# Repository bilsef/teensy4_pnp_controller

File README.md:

# teensy4_pnp_controller

# UNTESTED - USE AT YOUR OWN RISK
Preliminary testing shows everything working

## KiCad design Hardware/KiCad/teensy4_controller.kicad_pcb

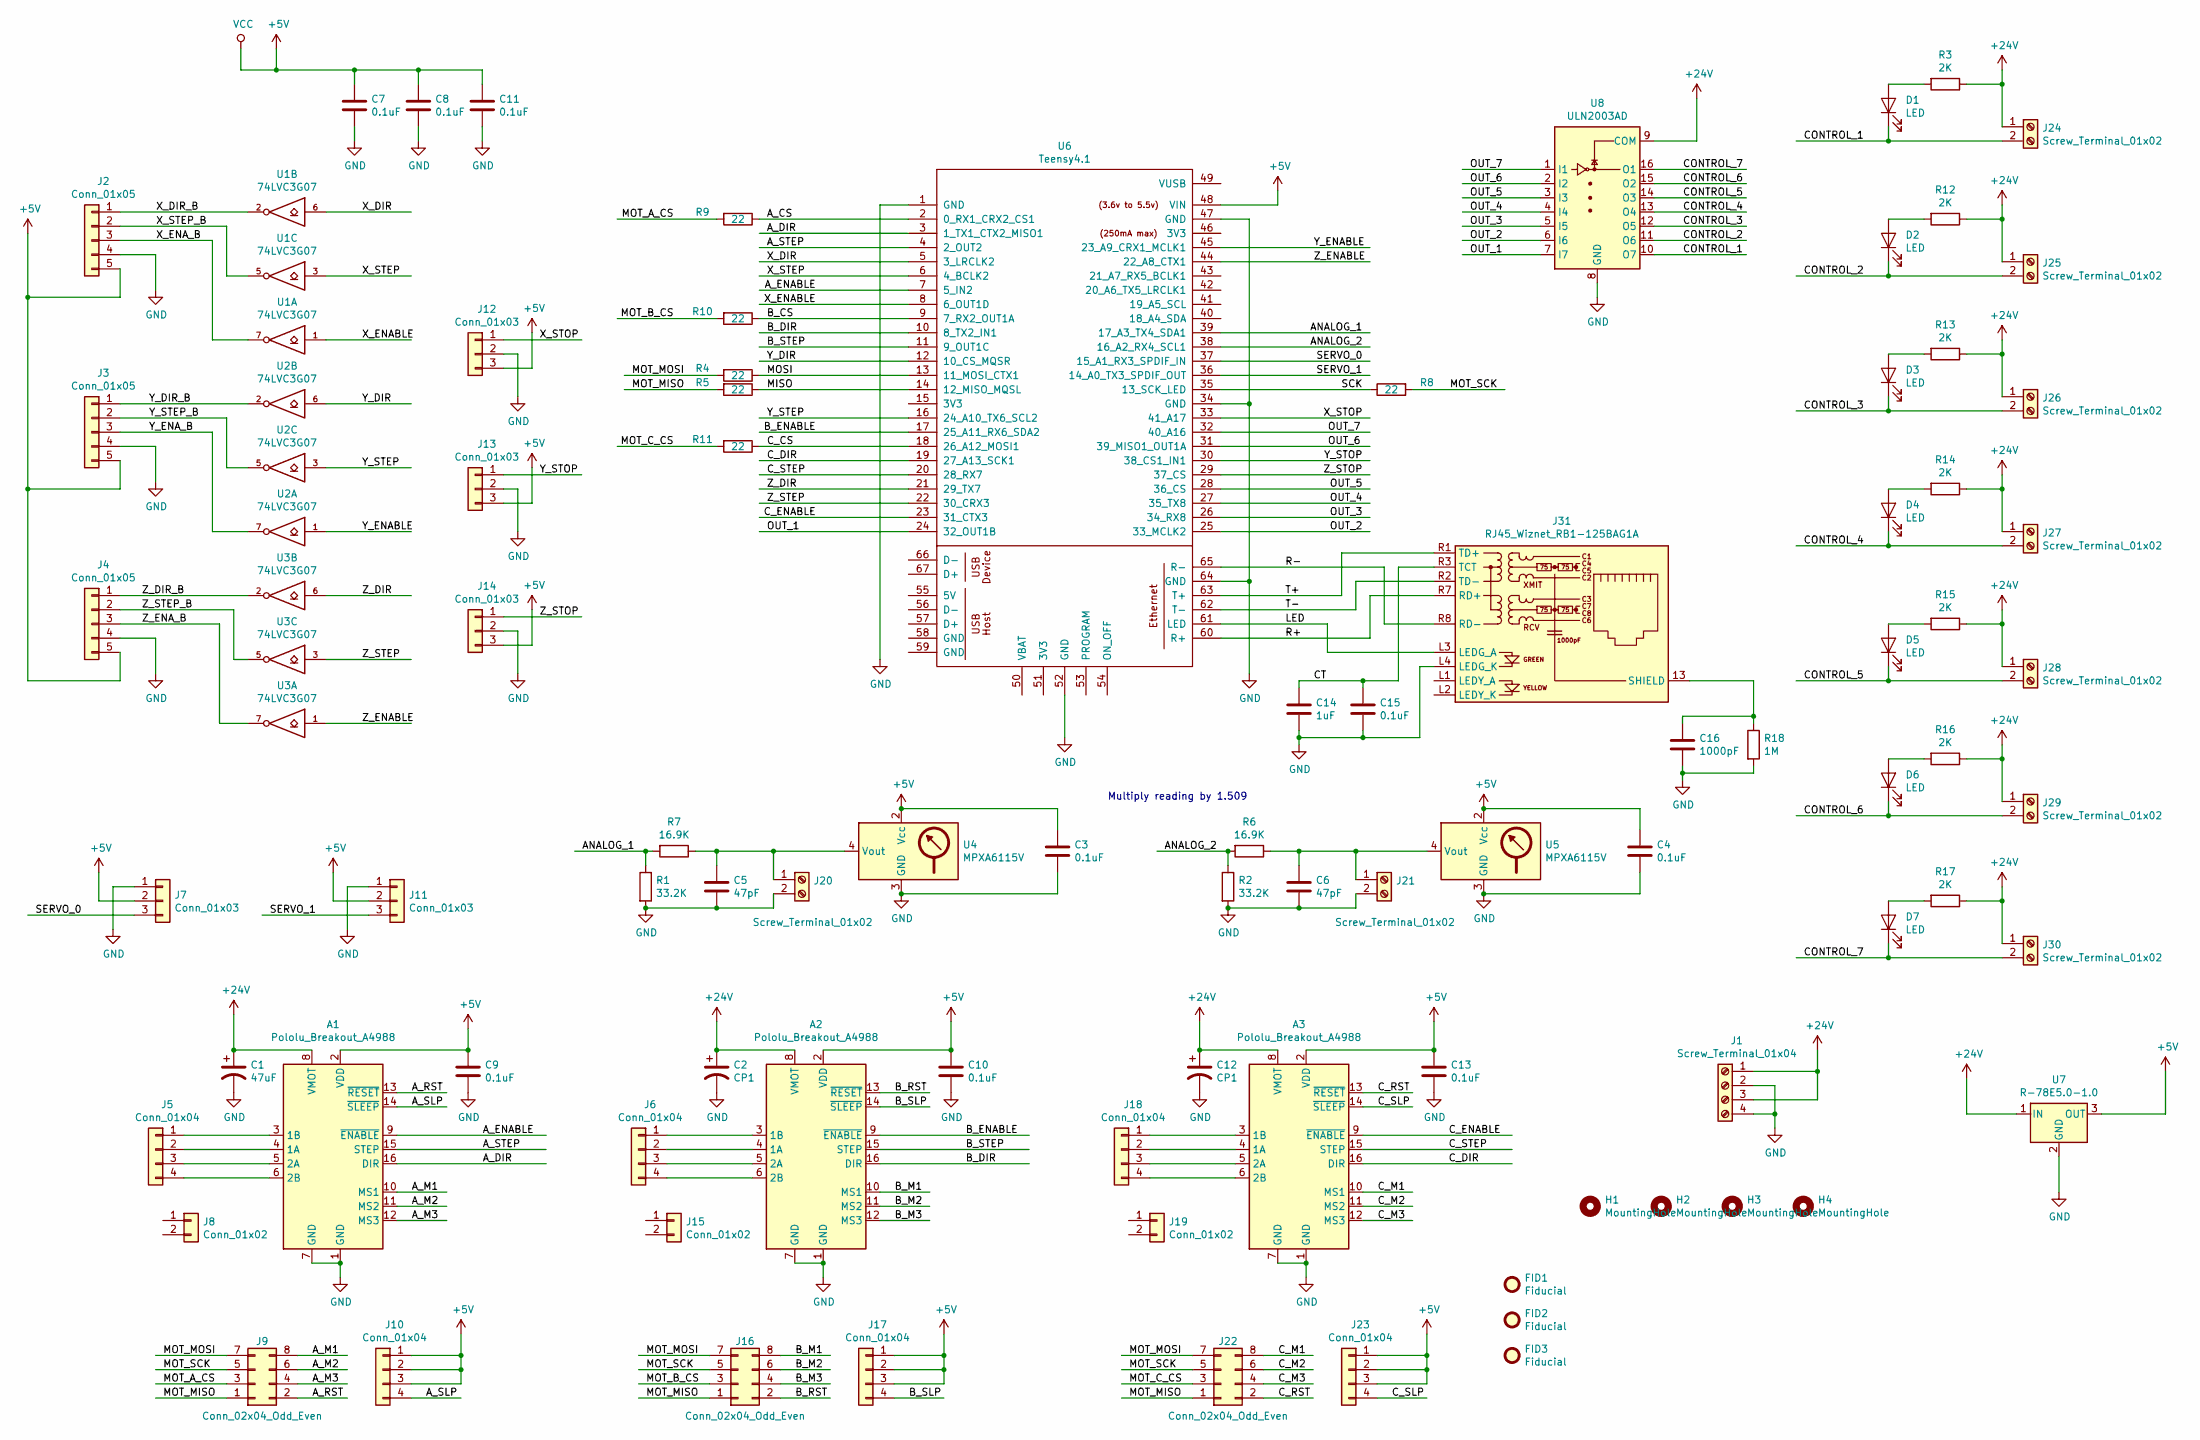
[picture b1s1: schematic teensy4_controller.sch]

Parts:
A1, A2, A3: Pololu_Breakout_A4988; Pololu_Breakout-16_15.2x20.3mm
C1: 47uF; CP_Elec_6.3x7.7
C2, C12: CP1; CP_Elec_6.3x7.7
C3, C4, C7, C8, C9, C10, C11, C13, C15: 0.1uF; C_0603_1608Metric_Pad1.05x0.95mm_HandSolder
C5, C6: 47pF; C_0603_1608Metric_Pad1.05x0.95mm_HandSolder
C14: 1uF; C_0805_2012Metric_Pad1.15x1.40mm_HandSolder
C16: 1000pF; C_1210_3225Metric_Pad1.42x2.65mm_HandSolder
D1, D2, D3, D4, D5, D6, D7: LED; LED_0603_1608Metric_Pad1.05x0.95mm_HandSolder
FID1, FID2, FID3: Fiducial; Fiducial_1mm_Mask3mm
H1, H2, H3, H4: MountingHole; MountingHole_3.2mm_M3
J1: Screw_Terminal_01x04; TerminalBlock_Phoenix_MKDS-1,5-4_1x04_P5.00mm_Horizontal
J2, J3, J4: Conn_01x05; JST_XH_B5B-XH-AM_1x05_P2.50mm_Vertical
J5, J6, J18: Conn_01x04; JST_XH_B4B-XH-A_1x04_P2.50mm_Vertical
J7, J11: Conn_01x03; PinHeader_1x03_P2.54mm_Vertical
J8, J15, J19: Conn_01x02; PinHeader_1x02_P2.54mm_Vertical
J9, J16, J22: Conn_02x04_Odd_Even; PinHeader_2x04_P2.54mm_Vertical
J10, J17, J23: Conn_01x04; PinHeader_1x04_P2.54mm_Vertical
J12, J13, J14: Conn_01x03; JST_XH_B3B-XH-AM_1x03_P2.50mm_Vertical
J20, J21, J24, J25, J26, J27, J28, J29, J30: Screw_Terminal_01x02; TerminalBlock_Phoenix_PT-1,5-2-3.5-H_1x02_P3.50mm_Horizontal
J31: RJ45_Wiznet_RB1-125BAG1A; RJ45_Amphenol_RJMG1BD3B8K1ANR
R1, R2: 33.2K; R_0603_1608Metric_Pad1.05x0.95mm_HandSolder
R3, R12, R13, R14, R15, R16, R17: 2K; R_0603_1608Metric_Pad1.05x0.95mm_HandSolder
R4, R5, R8, R9, R10, R11: 22; R_0603_1608Metric_Pad1.05x0.95mm_HandSolder
R6, R7: 16.9K; R_0603_1608Metric_Pad1.05x0.95mm_HandSolder
R18: 1M; R_0603_1608Metric_Pad1.05x0.95mm_HandSolder
U1, U2, U3: 74LVC3G07; VSSOP-8_3.0x3.0mm_P0.65mm
U4, U5: MPXA6115V; MPXA6115A
U6: Teensy4.1; Teensy41
U7: R-78E5.0-1.0; Converter_DCDC_RECOM_R-78E-0.5_THT
U8: ULN2003AD; SOIC-16_3.9x9.9mm_P1.27mm

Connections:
+5V: A1.2 (VDD), A2.2 (VDD), A3.2 (VDD), C3.1, C4.1, C7.1, C8.1, C9.1, C10.1, C11.1, C13.1, J2.5, J3.5, J4.5, J7.2, J10.1, J10.2, J10.3, J11.2, J12.3, J13.3, J14.3, J17.1, J17.2, J17.3, J23.1, J23.2, J23.3, U1.8 (VCC), U2.8 (VCC), U3.8 (VCC), U4.2 (Vcc), U5.2 (Vcc), U6.48 (VIN), U7.3 (OUT)
+24V: A1.8 (VMOT), A2.8 (VMOT), A3.8 (VMOT), C1.1, C2.1, C12.1, J1.1, J1.3, J24.1, J25.1, J26.1, J27.1, J28.1, J29.1, J30.1, R3.1, R12.1, R13.1, R14.1, R15.1, R16.1, R17.1, U7.1 (IN), U8.9 (COM)
/ANALOG_1: R1.1, R7.2, U6.39 (17_A3_TX4_SDA1)
/ANALOG_2: R2.1, R6.2, U6.38 (16_A2_RX4_SCL1)
/A_CS: R9.1, U6.2 (0_RX1_CRX2_CS1)
/A_DIR: A1.16 (DIR), U6.3 (1_TX1_CTX2_MISO1)
/A_ENABLE: A1.9 (~ENABLE), U6.7 (5_IN2)
/A_M1: A1.10 (MS1), J9.8
/A_M2: A1.11 (MS2), J9.6
/A_M3: A1.12 (MS3), J9.4
/A_RST: A1.13 (~RESET), J9.2
/A_SLP: A1.14 (~SLEEP), J10.4
/A_STEP: A1.15 (STEP), U6.4 (2_OUT2)
/B_CS: R10.1, U6.9 (7_RX2_OUT1A)
/B_DIR: A2.16 (DIR), U6.10 (8_TX2_IN1)
/B_ENABLE: A2.9 (~ENABLE), U6.17 (25_A11_RX6_SDA2)
/B_M1: A2.10 (MS1), J16.8
/B_M2: A2.11 (MS2), J16.6
/B_M3: A2.12 (MS3), J16.4
/B_RST: A2.13 (~RESET), J16.2
/B_SLP: A2.14 (~SLEEP), J17.4
/B_STEP: A2.15 (STEP), U6.11 (9_OUT1C)
/CONTROL_1: D1.1 (K), J24.2, U8.10 (O7)
/CONTROL_2: D2.1 (K), J25.2, U8.11 (O6)
/CONTROL_3: D3.1 (K), J26.2, U8.12 (O5)
/CONTROL_4: D4.1 (K), J27.2, U8.13 (O4)
/CONTROL_5: D5.1 (K), J28.2, U8.14 (O3)
/CONTROL_6: D6.1 (K), J29.2, U8.15 (O2)
/CONTROL_7: D7.1 (K), J30.2, U8.16 (O1)
/CT: C14.1, C15.1, J31.R3 (TCT)
/C_CS: R11.1, U6.18 (26_A12_MOSI1)
/C_DIR: A3.16 (DIR), U6.19 (27_A13_SCK1)
/C_ENABLE: A3.9 (~ENABLE), U6.23 (31_CTX3)
/C_M1: A3.10 (MS1), J22.8
/C_M2: A3.11 (MS2), J22.6
/C_M3: A3.12 (MS3), J22.4
/C_RST: A3.13 (~RESET), J22.2
/C_SLP: A3.14 (~SLEEP), J23.4
/C_STEP: A3.15 (STEP), U6.20 (28_RX7)
/LED: J31.L3 (LEDG_A), U6.61 (LED)
/MISO: R5.1, U6.14 (12_MISO_MQSL)
/MOSI: R4.1, U6.13 (11_MOSI_CTX1)
/MOT_A_CS: J9.3, R9.2
/MOT_B_CS: J16.3, R10.2
/MOT_C_CS: J22.3, R11.2
/MOT_MISO: J9.1, J16.1, J22.1, R5.2
/MOT_MOSI: J9.7, J16.7, J22.7, R4.2
/MOT_SCK: J9.5, J16.5, J22.5, R8.2
/OUT_1: U6.24 (32_OUT1B), U8.7 (I7)
/OUT_2: U6.25 (33_MCLK2), U8.6 (I6)
/OUT_3: U6.26 (34_RX8), U8.5 (I5)
/OUT_4: U6.27 (35_TX8), U8.4 (I4)
/OUT_5: U6.28 (36_CS), U8.3 (I3)
/OUT_6: U6.31 (39_MISO1_OUT1A), U8.2 (I2)
/OUT_7: U6.32 (40_A16), U8.1 (I1)
/R+: J31.R7 (RD+), U6.60 (R+)
/R-: J31.R8 (RD-), U6.65 (R-)
/SCK: R8.1, U6.35 (13_SCK_LED)
/SERVO_0: J7.3, U6.37 (15_A1_RX3_SPDIF_IN)
/SERVO_1: J11.3, U6.36 (14_A0_TX3_SPDIF_OUT)
/T+: J31.R1 (TD+), U6.63 (T+)
/T-: J31.R2 (TD-), U6.62 (T-)
/X_DIR: U1.6, U6.5 (3_LRCLK2)
/X_DIR_B: J2.1, U1.2
/X_ENABLE: U1.1, U6.8 (6_OUT1D)
/X_ENA_B: J2.3, U1.7
/X_STEP: U1.3, U6.6 (4_BCLK2)
/X_STEP_B: J2.2, U1.5
/X_STOP: J12.1, U6.33 (41_A17)
/Y_DIR: U2.6, U6.12 (10_CS_MQSR)
/Y_DIR_B: J3.1, U2.2
/Y_ENABLE: U2.1, U6.45 (23_A9_CRX1_MCLK1)
/Y_ENA_B: J3.3, U2.7
/Y_STEP: U2.3, U6.16 (24_A10_TX6_SCL2)
/Y_STEP_B: J3.2, U2.5
/Y_STOP: J13.1, U6.30 (38_CS1_IN1)
/Z_DIR: U3.6, U6.21 (29_TX7)
/Z_DIR_B: J4.1, U3.2
/Z_ENABLE: U3.1, U6.44 (22_A8_CTX1)
/Z_ENA_B: J4.3, U3.7
/Z_STEP: U3.3, U6.22 (30_CRX3)
/Z_STEP_B: J4.2, U3.5
/Z_STOP: J14.1, U6.29 (37_CS)
GND: A1.1 (GND), A1.7 (GND), A2.1 (GND), A2.7 (GND), A3.1 (GND), A3.7 (GND), C1.2, C2.2, C3.2, C4.2, C5.2, C6.2, C7.2, C8.2, C9.2, C10.2, C11.2, C12.2, C13.2, C14.2, C15.2, C16.2, J1.2, J1.4, J2.4, J3.4, J4.4, J7.1, J11.1, J12.2, J13.2, J14.2, J20.2, J21.2, J31.L4 (LEDG_K), R1.2, R2.2, R18.2, U1.4 (GND), U2.4 (GND), U3.4 (GND), U4.3 (GND), U5.3 (GND), U6.1 (GND), U6.34 (GND), U6.47 (GND), U6.52 (GND), U6.64 (GND), U7.2 (GND), U8.8 (GND)
unnamed: A1.3 (1B), J5.1
unnamed: A1.4 (1A), J5.2
unnamed: A1.5 (2A), J5.3
unnamed: A1.6 (2B), J5.4
unnamed: A2.3 (1B), J6.1
unnamed: A2.4 (1A), J6.2
unnamed: A2.5 (2A), J6.3
unnamed: A2.6 (2B), J6.4
unnamed: A3.3 (1B), J18.1
unnamed: A3.4 (1A), J18.2
unnamed: A3.5 (2A), J18.3
unnamed: A3.6 (2B), J18.4
unnamed: C5.1, J20.1, R7.1, U4.4 (Vout)
unnamed: C6.1, J21.1, R6.1, U5.4 (Vout)
unnamed: C16.1, J31.13 (SHIELD), R18.1
unnamed: D1.2 (A), R3.2
unnamed: D2.2 (A), R12.2
unnamed: D3.2 (A), R13.2
unnamed: D4.2 (A), R14.2
unnamed: D5.2 (A), R15.2
unnamed: D6.2 (A), R16.2
unnamed: D7.2 (A), R17.2

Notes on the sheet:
Multiply reading by 1.509

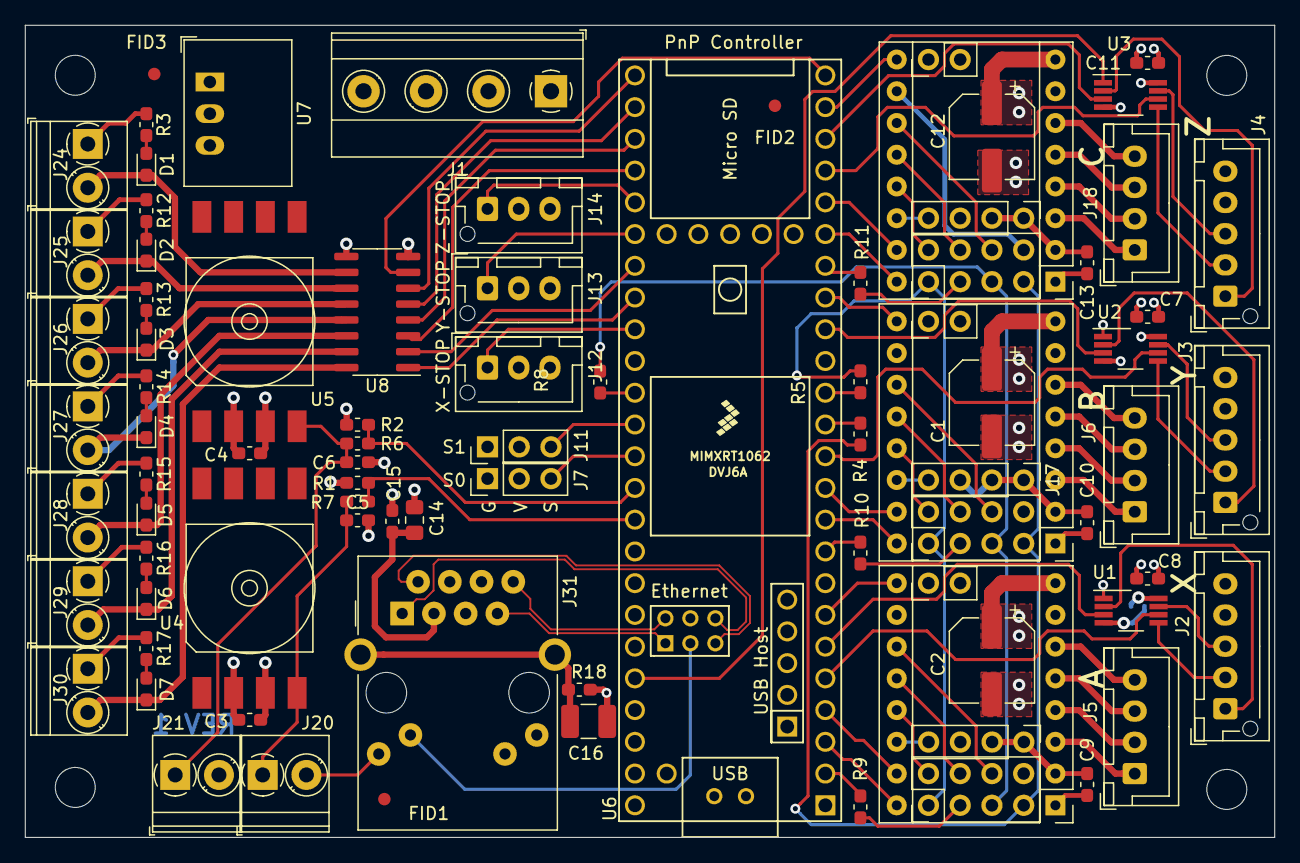
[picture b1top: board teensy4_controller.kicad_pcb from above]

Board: 4 copper layers, 100.0 x 65.0 mm, 90 parts (0 on the bottom side), 106 nets.

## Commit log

2020-08-21 Update
    As ordered
2020-09-03 Correct error on TMC SPI connections
    MISO and CS were swapped at config jumpers
2020-09-06 Rev 2
    Improve silkscreen
    Changed footprint name of 74LVC3G07 from VSSOP-8 to TSSOP-8
